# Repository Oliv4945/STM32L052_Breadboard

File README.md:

# STM32L052 Breadboard
Small breadboard compatible development board designed for STM32L052, but all STM32 in LQFP32 package should fit.

# Requirements
* Breakout all I/Os
* WS2812 RGB led, blinky things, you know !
* 3.3V LDO regulator
* Easy way to select Vin or Vusb (jumper)
* Easy way to select `BOOT0` (jumper)
* USB connector and ESD protection
* 200 to 300 mA mosfet in order to control a more power or other voltages
* Reset button
* Breadboard friendly
* "FTDI" pinout connector for serial communications, and to try ST serial bootloader
* All components on one side, so the board can be easily reflowed with hotplate

# Toolchain
Example projets are for Eclipse/OpenSTM32/GCC-ARM, also CubeMX project file is given so it should be easy to generate project files for other IDE.

# Code examples
There is few snippets of code in master branch, regarding:
* WS2812b led
* MOSFET control
* RTC  

In USB_HID branch, there is custom USB_HID device which allows consumer device (media keys) + keyboard

# Others
More info [here](http://notes.iopush.net/stm32l052-development-board/).  
Hardware is under CC Attribution-ShareAlike 3.0 license.

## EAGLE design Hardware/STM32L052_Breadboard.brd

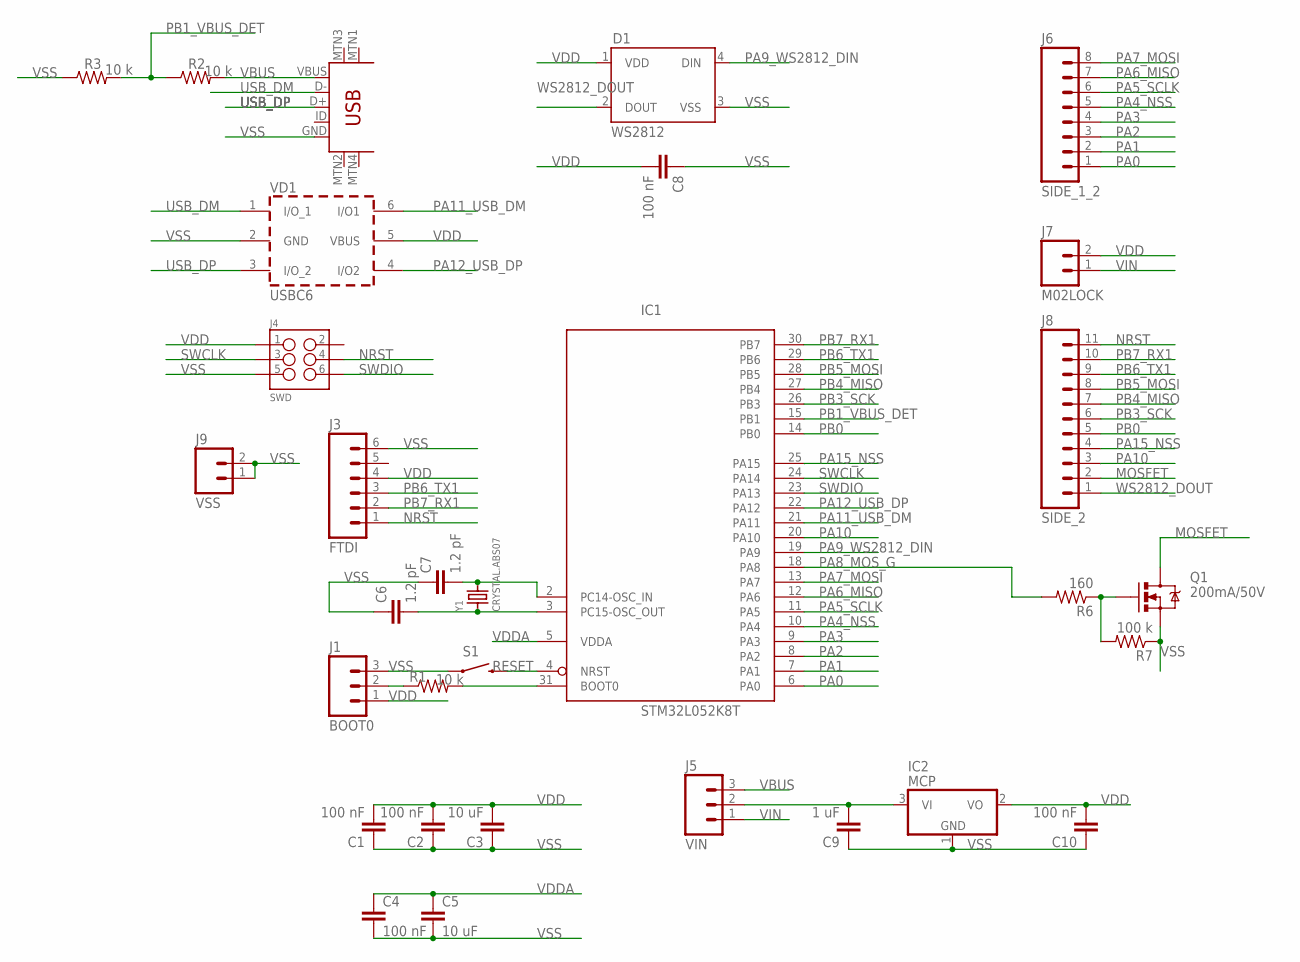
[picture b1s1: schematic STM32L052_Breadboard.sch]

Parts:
C1, C2, C4, C8, C10: 100 nF; 0603-CAP
C3, C5: 10 uF; 0603-CAP
C6, C7: 1.2 pF; 0603-CAP
C9: 1 uF; 0603-CAP
D1: WS2812; WS2812B
IC1: STM32L052K8T; LQFP32
IC2: MCP; SOT23
J1: BOOT0; 1X03_LOCK
J3: FTDI; 1X06_LOCK
J4: SWD; 2X3
J5: VIN; 1X03_LOCK
J6: SIDE_1_2; 1X08_LOCK
J7: M02LOCK; 1X02_LOCK
J8: SIDE_2; 1X11_LOCK
J9: VSS; 1X02_LOCK
Q1: 200mA/50V; SOT23-3
R1, R2, R3: 10 k; 0603-RES
R6: 160; 0805
R7: 100 k; 0805
S1: RESET; TACTILE-SWITCH-SMD
U$1: USB-MINIB-5PIN; USB-MINIB
VD1: USBC6; SOT-23-6L
Y1: CRYSTAL.ABS07; ABS07

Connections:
BOOT0: IC1.31 (BOOT0), R1.2
BOOT0_SEL: J1.2, R1.1
MOSFET: J8.2, Q1.3 (D)
unnamed: Q1.1 (G), R6.1, R7.2
NRST: IC1.4 (NRST), J3.1, J4.4, J8.11, S1.3 (2)
OSC_IN: C7.2, IC1.2 (PC14-OSC_IN), Y1.2
OSC_OUT: C6.2, IC1.3 (PC15-OSC_OUT), Y1.1
PA0: IC1.6 (PA0), J6.1
PA1: IC1.7 (PA1), J6.2
PA2: IC1.8 (PA2), J6.3
PA3: IC1.9 (PA3), J6.4
PA4_NSS: IC1.10 (PA4), J6.5
PA5_SCLK: IC1.11 (PA5), J6.6
PA6_MISO: IC1.12 (PA6), J6.7
PA7_MOSI: IC1.13 (PA7), J6.8
PA8_MOS_G: IC1.18 (PA8), R6.2
PA9_WS2812_DIN: D1.4 (DIN), IC1.19 (PA9)
PA10: IC1.20 (PA10), J8.3
PA11_USB_DM: IC1.21 (PA11), VD1.6 (I/O1)
PA12_USB_DP: IC1.22 (PA12), VD1.4 (I/O2)
PA15_NSS: IC1.25 (PA15), J8.4
PB0: IC1.14 (PB0), J8.5
PB1_VBUS_DET: IC1.15 (PB1), R2.1, R3.2
PB3_SCK: IC1.26 (PB3), J8.6
PB4_MISO: IC1.27 (PB4), J8.7
PB5_MOSI: IC1.28 (PB5), J8.8
PB6_TX1: IC1.29 (PB6), J3.3, J8.9
PB7_RX1: IC1.30 (PB7), J3.2, J8.10
SWCLK: IC1.24 (PA14), J4.3
SWDIO: IC1.23 (PA13), J4.6
USB_DM: U$1.D-, VD1.1 (I/O_1)
USB_DP: U$1.D+, VD1.3 (I/O_2)
VBUS: J5.3, R2.2, U$1.VBUS
VDD: C1.2, C2.2, C3.2, C8.2, C10.2, D1.1 (VDD), IC1.1 (VDD), IC1.17 (VDD), IC2.2 (VO), J1.1, J3.4, J4.1, J7.2, VD1.5 (VBUS)
VDDA: C4.1, C5.1, IC1.5 (VDDA)
VIN: J5.1, J7.1
VIN_ALL: C9.2, IC2.3 (VI), J5.2
VSS: C1.1, C2.1, C3.1, C4.2, C5.2, C6.1, C7.1, C8.1, C9.1, C10.1, D1.3 (VSS), IC1.16 (VSS), IC1.32 (VSS), IC2.1 (GND), J1.3, J3.6, J4.5, J9.1, J9.2, Q1.2 (S), R3.1, R7.1, S1.1, U$1.GND, VD1.2 (GND)
WS2812_DOUT: D1.2 (DOUT), J8.1

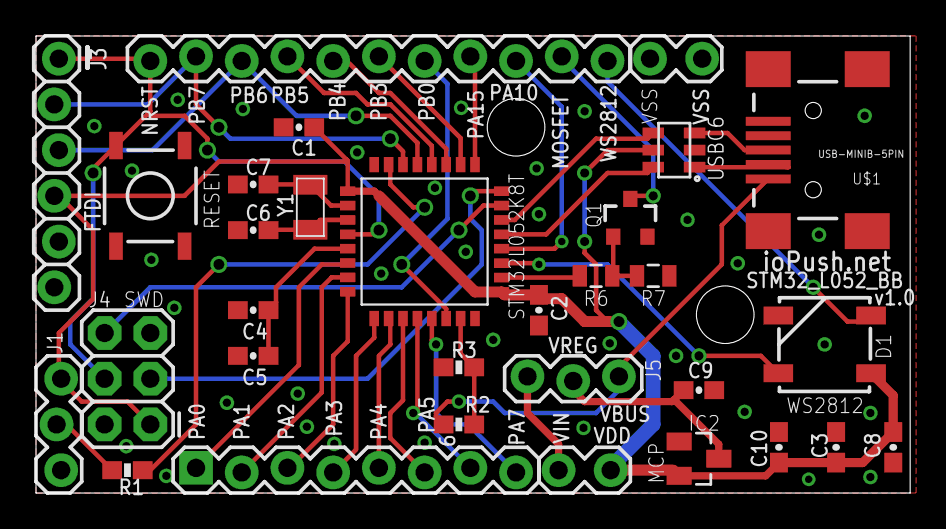
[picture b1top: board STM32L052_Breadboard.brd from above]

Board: 2 copper layers, 48.6 x 25.4 mm, 31 parts (0 on the bottom side), 39 nets.

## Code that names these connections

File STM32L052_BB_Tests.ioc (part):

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Mcu.Name=STM32L052K(6-8)Tx
Mcu.Package=LQFP32
Mcu.UserName=STM32L052K8Tx
PA11.Mode=Device
PA11.Signal=USB_DM
PA12.Mode=Device
PA12.Signal=USB_DP
PA8.GPIOParameters=GPIO_Label
PA8.GPIO_Label=MOSFET
PA8.Signal=GPIO_Output
PA9.GPIOParameters=GPIO_Label
PA9.GPIO_Label=WS2812
PA9.Signal=GPIO_Output
PB6.Mode=Asynchronous
PB6.Signal=USART1_TX
PB7.Mode=Asynchronous
PB7.Signal=USART1_RX
PC14-OSC32_IN.Mode=LSE-External-Oscillator
PC14-OSC32_IN.Signal=RCC_OSC32_IN
PC15-OSC32_OUT.Mode=LSE-External-Oscillator
PC15-OSC32_OUT.Signal=RCC_OSC32_OUT
RCC.SYSCLKFreq_VALUE=16000000
RCC.SYSCLKSource=RCC_SYSCLKSOURCE_HSI
board=STM32L052_BB_Tests

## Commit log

2016-11-29 Untrack Debug folder
2016-12-11 Switch RTC to binary mode
2016-12-11 Init WS2812B
2016-12-11 Add MOSFET
2016-12-11 WS2812B works, clock<= 16 MHz for 0 wait state
2016-12-11 Switch light_ws2812 to forked repository
2016-12-11 Add documents
2016-12-11 Add hardware design files
2016-12-11 Add README.md file
2016-12-15 Add ST HID mouse example
2016-12-16 Change example to custom descriptor (media+keyboard)
2016-12-16 Update Readme with USB_HID
2017-02-20 Typo correction - Error byte note aligned
    But was working on MacOS !?

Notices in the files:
parts and their libraries:
SparkFun-Capacitors: Licensing: Creative Commons ShareAlike 4.0 International - https://creativecommons.org/licenses/by-sa/4.0
